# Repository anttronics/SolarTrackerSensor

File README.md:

## SolarTrackerSensor
A simple sensor circuit that uses photo-transistors and boolean logic to indicate if a solar panel is pointing straight at the sun. 

### Outputs 
- It produces 4 digital outputs to indicate if movement is required in up, down, left or right directions. Those outputs can be passed directly to a motor controller which can correct the mis-alignment. 
- It also produces horizontal, vertical and combined "busy" signals to allow independent, as well as overall enabling/disabling of the motors.

**Warning**: All outputs are unprotected, digital signal outputs and should not be used to drive any motors directly.

### Limit Switches
It has normally-closed (NC) limit switch inputs for all 4 directions, but requires at least the "east" and "down" switches for auto-parking to function. The "west" and "up" limit switches can be omitted/bypassed if the motion mechanism has sufficient range and/or limits implemented elsewhere.

### Auto-parking
When the ambient light level falls below the adjustable threshold, it will auto-park the panel in the "east" and "down" position. Without the auto-park function, in the summer months, the panel would be left pointing west at sunset. The sun would then rise behind the panel and tracking would not resume until late morning, when the sun moves n front of the panel again.

### Sensitivity
A common reference level for all 4 comparators is produced using a potentiometer as a voltage divider. The simplest way to set the sensitivity is to adjust it on a dark cloudy day, to a level just above the parking level. This way it won't try to auto-park the panel every time a cloud moves across the sun. 

### Assembly
The board is designed in 3 parts: 
- the "logic" part which contains all the main components,
- the "sensor" part which contains the photo-transistors and
- the "shield" parts. 

The "sensor" board has the same footprints on both sides, allowing assembly on the "N" or "S" side, depending on whether the sun will be tracked from the north or south hemisphere.

It can be separated from the "logic" board and connected with wires, or it can be kept attached to the "logic" board. The traces between the boards complete all the required connections between the two boards.

The "shield" parts, when soldered onto the "sensor" board, form a pyramid-shaped sun screen that cast a shadow on the photo-transistors when the panel is not correctly aligned.

### Power supply
Even though all the components on the board could handle a higher voltage, a stable 5V DC power supply is highly recommended to ensure the reference levels for the comparator are actually effective. 

### Future ideas
- Motor control board with sleep/periodic wake-up function for low power consumption
- Battery charging board with constant panel voltage or MPP tracking.

### How did we get here?
The prototype "ancestor" of this board has been keeping an A4-size 4V panel pointed at the sun through my office window for a few years already. It charges a 2S LiPo battery during the day which in turn is used as a power bank to charge my phone. 

The mechanical construction is showing its age and needs an overhaul. The plan is to switch from continuous rotation servos to DC gear motors for smoother movement and in the process, try to tidy up the electronics as well.

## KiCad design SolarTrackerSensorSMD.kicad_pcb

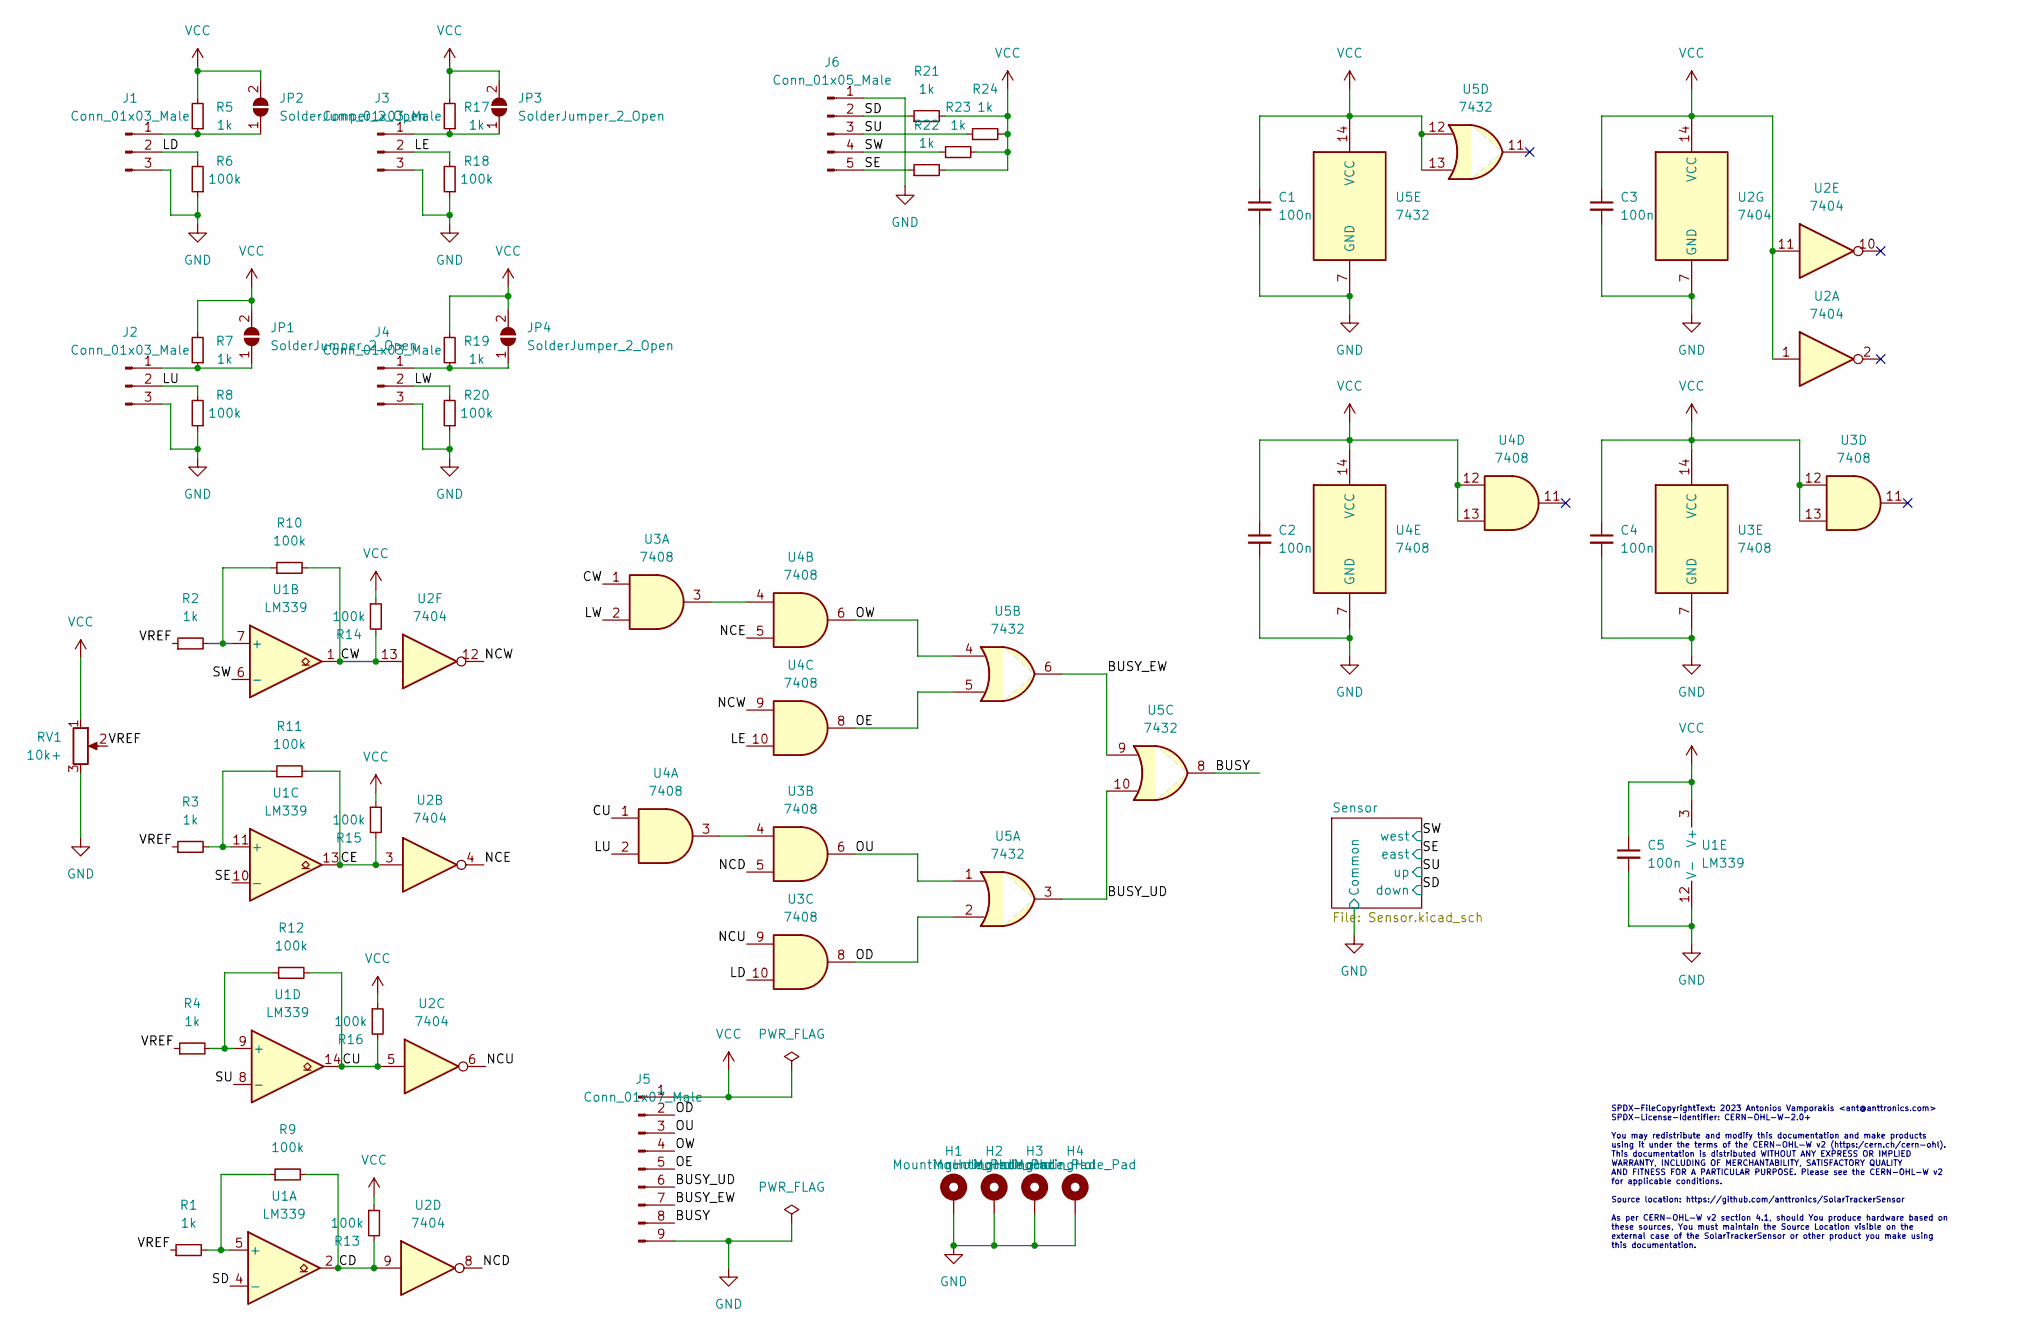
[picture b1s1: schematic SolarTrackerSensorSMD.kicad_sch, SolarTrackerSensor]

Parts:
C1, C2, C3, C4, C5: 100n; C_0603_1608Metric; MPN C282519
H1, H2, H3, H4: MountingHole_Pad; MountingHole_3.2mm_M3_DIN965_Pad
J1, J2, J3, J4: Conn_01x03_Male; PinHeader_1x03_P2.54mm_Vertical
J5: Conn_01x07_Male; PinHeader_1x09_P2.54mm_Vertical
J6: Conn_01x05_Male; PinHeader_1x05_P2.54mm_Vertical
JP1, JP2, JP3, JP4: SolderJumper_2_Open; SolderJumper-2_P1.3mm_Open_RoundedPad1.0x1.5mm
R1, R2, R3, R4, R5, R7, R17, R19, R21, R22, R23, R24: 1k; R_0603_1608Metric; MPN C3152127
R6, R8, R9, R10, R11, R12, R13, R14, R15, R16, R18, R20: 100k; R_0603_1608Metric; MPN C2907088
RV1: 10k+; Potentiometer_Bourns_3296W_Vertical; MPN C118963
U1: LM339; SOIC-14_3.9x8.7mm_P1.27mm; MPN C5456631
U2: 7404; SOIC-14_3.9x8.7mm_P1.27mm; MPN C141316
U3, U4: 7408; SOIC-14_3.9x8.7mm_P1.27mm; MPN C337768
U5: 7432; SOIC-14_3.9x8.7mm_P1.27mm; MPN C132988

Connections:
/BUSY: J5.8, U5.8
/BUSY_EW: J5.7, U5.6, U5.9
/BUSY_UD: J5.6, U5.3, U5.10
/CD: R9.2, R13.2, U1.2, U2.9
/CE: R11.2, R15.2, U1.13, U2.3
/CU: R12.2, R16.2, U1.14, U2.5, U4.1
/CW: R10.2, R14.2, U1.1, U2.13, U3.1
/LD: J1.2, R6.2, U3.10
/LE: J3.2, R18.2, U4.10
/LU: J2.2, R8.2, U4.2
/LW: J4.2, R20.2, U3.2
/NCD: U2.8, U3.5
/NCE: U2.4, U4.5
/NCU: U2.6, U3.9
/NCW: U2.12, U4.9
/OD: J5.2, U3.8, U5.2
/OE: J5.5, U4.8, U5.5
/OU: J5.3, U3.6, U5.1
/OW: J5.4, U4.6, U5.4
/SD: J6.2, R21.1, U1.4 (-); also elsewhere on the board
/SE: J6.5, R22.1, U1.10 (-); also elsewhere on the board
/SU: J6.3, R24.1, U1.8 (-); also elsewhere on the board
/SW: J6.4, R23.1, U1.6 (-); also elsewhere on the board
/VREF: R1.1, R2.1, R3.1, R4.1, RV1.2
GND: C1.2, C2.2, C3.2, C4.2, C5.2, H1.1, H2.1, H3.1, H4.1, J1.3, J2.3, J3.3, J4.3, J5.9, J6.1, R6.1, R8.1, R18.1, R20.1, RV1.3, U1.12 (V-), U2.7 (GND), U3.7 (GND), U4.7 (GND), U5.7 (GND); also elsewhere on the board
unnamed: J1.1, JP2.1 (A), R5.1
unnamed: J2.1, JP1.1 (A), R7.1
unnamed: J3.1, JP3.1 (A), R17.1
unnamed: J4.1, JP4.1 (A), R19.1
unnamed: R1.2, R9.1, U1.5 (+)
unnamed: R2.2, R10.1, U1.7 (+)
unnamed: R3.2, R11.1, U1.11 (+)
unnamed: R4.2, R12.1, U1.9 (+)
unnamed: U3.3, U4.4
unnamed: U3.4, U4.3
VCC: C1.1, C2.1, C3.1, C4.1, C5.1, J5.1, JP1.2 (B), JP2.2 (B), JP3.2 (B), JP4.2 (B), R5.2, R7.2, R13.1, R14.1, R15.1, R16.1, R17.2, R19.2, R21.2, R22.2, R23.2, R24.2, RV1.1, U1.3 (V+), U2.1, U2.11, U2.14 (VCC), U3.12, U3.13, U3.14 (VCC), U4.12, U4.13, U4.14 (VCC), U5.12, U5.13, U5.14 (VCC)

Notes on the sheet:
SPDX-FileCopyrightText: 2023 Antonios Vamporakis <ant@anttronics.com> SPDX-License-Identifier: CERN-OHL-W-2.0+ You may redistribute and modify this documentation and make products using it under the terms of the CERN-OHL-W v2 (https:/cern.ch/cern-ohl). This documentation is distributed WITHOUT ANY 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

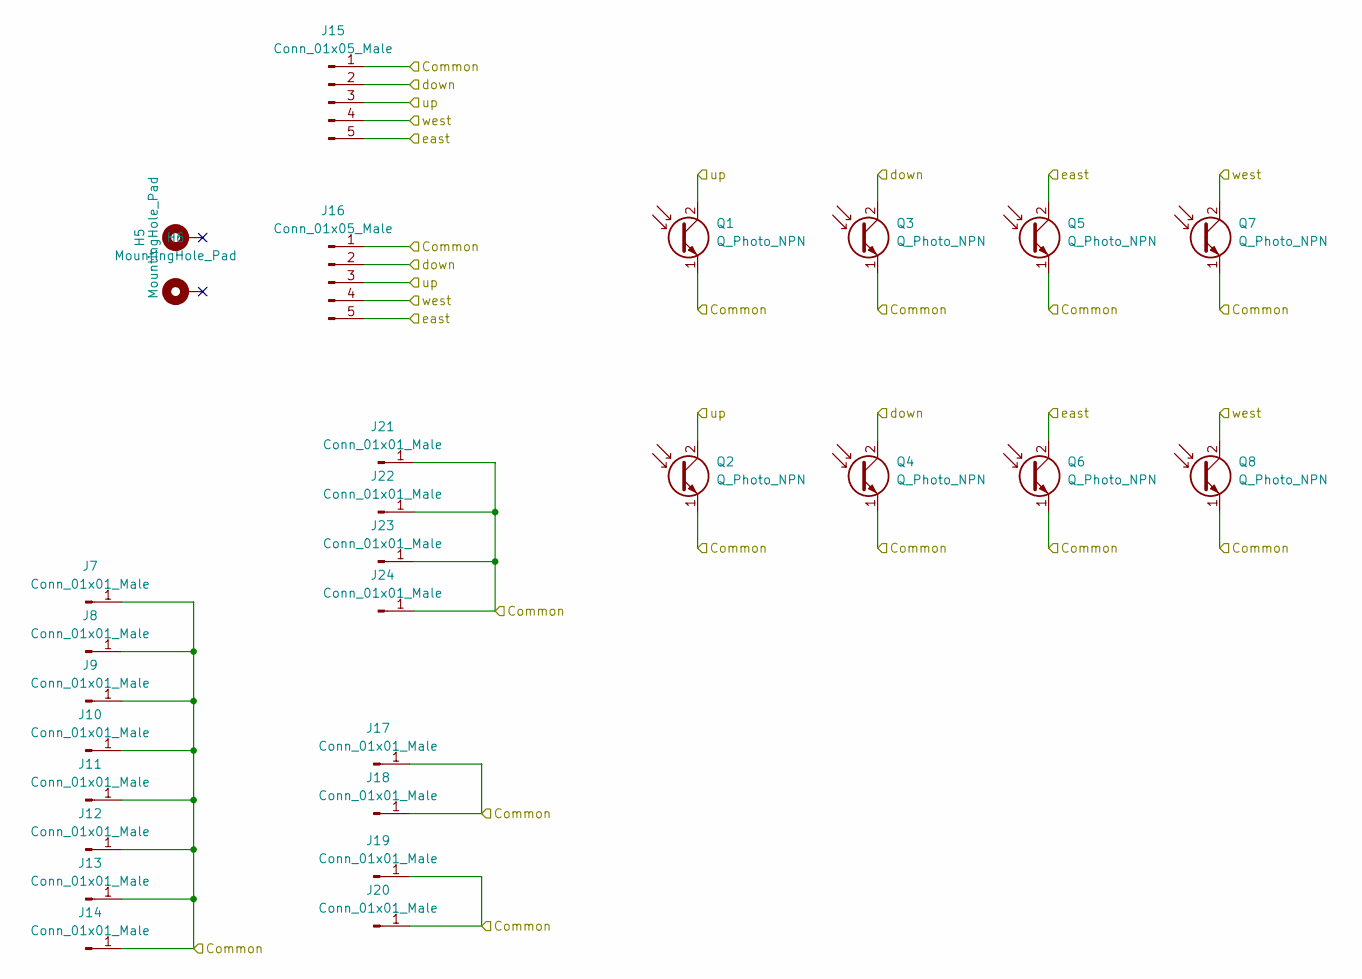
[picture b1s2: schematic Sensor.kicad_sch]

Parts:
H5, H6: MountingHole_Pad; MountingHole_3.2mm_M3_DIN965_Pad
J7, J8, J9, J10, J11, J12, J13, J14: Conn_01x01_Male; TestPoint_Pad_4.0x4.0mm
J15, J16: Conn_01x05_Male; PinHeader_1x05_P2.54mm_Vertical
J17, J18, J19, J20: Conn_01x01_Male; TestPoint_Pad_D4.0mm
J21, J22, J23, J24: Conn_01x01_Male; TestPoint_THTPad_D4.0mm_Drill2.0mm
Q1, Q2, Q3, Q4, Q5, Q6, Q7, Q8: Q_Photo_NPN; LED_0603_1608Metric; MPN C146233

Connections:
/SD: J15.2, J16.2, Q3.2 (C), Q4.2 (C); also elsewhere on the board
/SE: J15.5, J16.5, Q5.2 (C), Q6.2 (C); also elsewhere on the board
/SU: J15.3, J16.3, Q1.2 (C), Q2.2 (C); also elsewhere on the board
/SW: J15.4, J16.4, Q7.2 (C), Q8.2 (C); also elsewhere on the board
GND: J7.1, J8.1, J9.1, J10.1, J11.1, J12.1, J13.1, J14.1, J15.1, J16.1, J17.1, J18.1, J19.1, J20.1, J21.1, J22.1, J23.1, J24.1, Q1.1 (E), Q2.1 (E), Q3.1 (E), Q4.1 (E), Q5.1 (E), Q6.1 (E), Q7.1 (E), Q8.1 (E); also elsewhere on the board

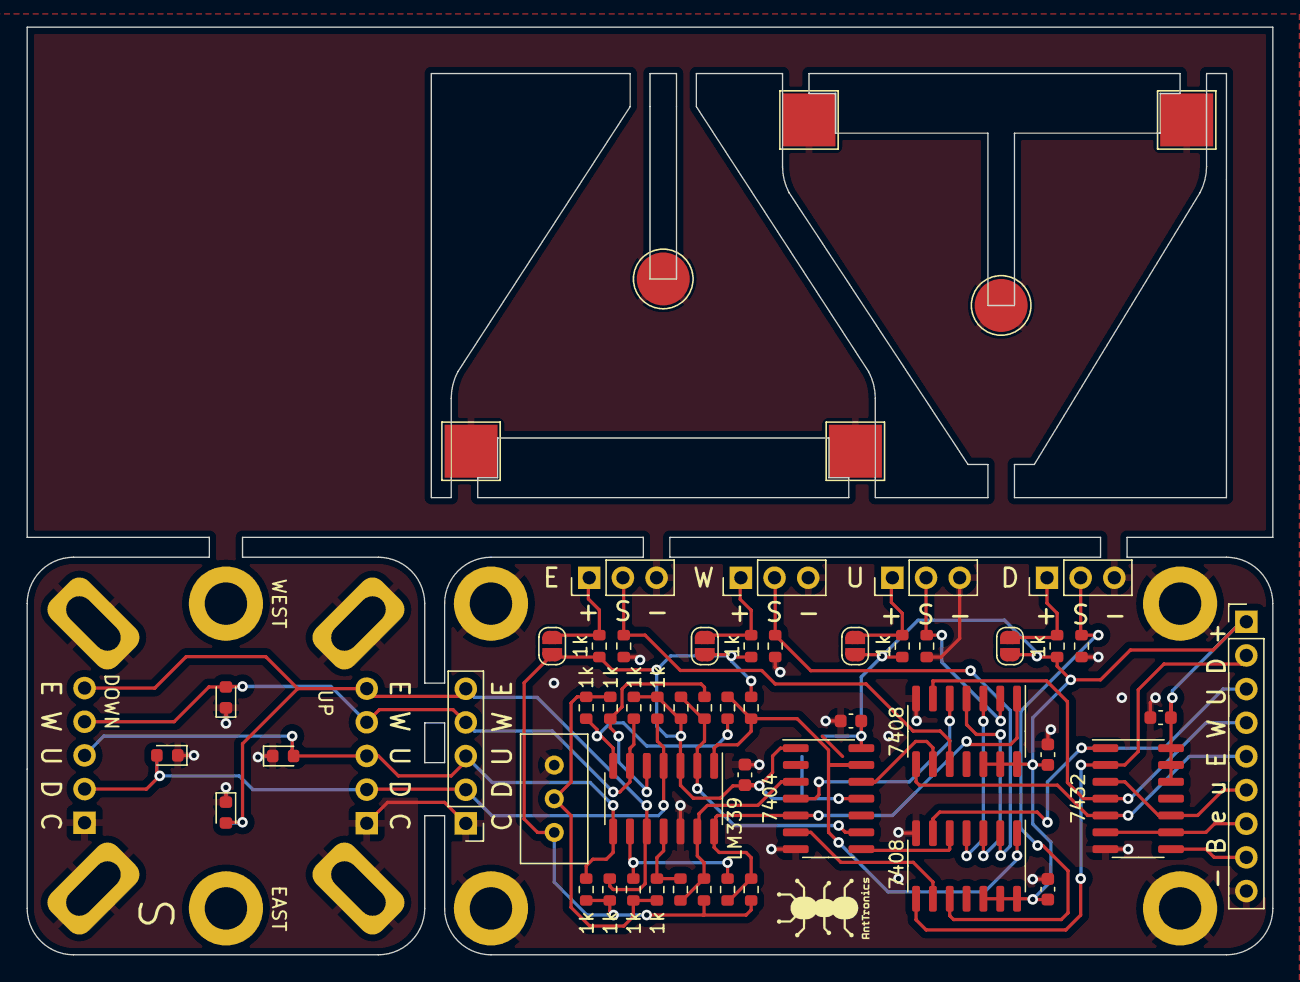
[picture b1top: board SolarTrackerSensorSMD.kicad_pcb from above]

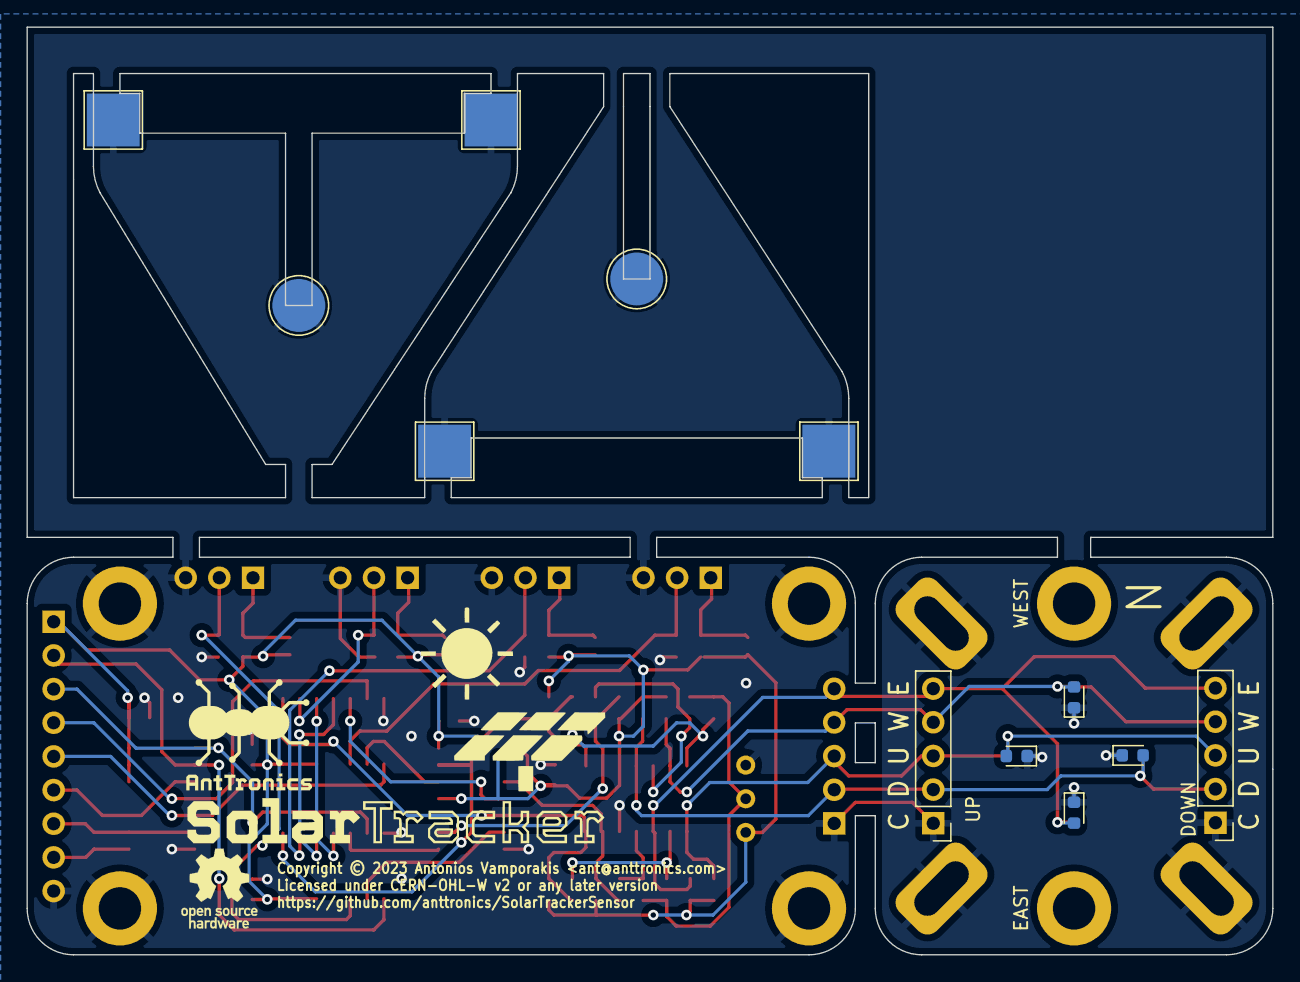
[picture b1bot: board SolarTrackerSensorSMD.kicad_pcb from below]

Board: 2 copper layers, 94.0 x 69.9 mm, 77 parts (12 on the bottom side), 36 nets.

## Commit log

2023-07-08 Replace Idle with Busy_UD & Busy_EW
2023-12-11 Remove ignored files
2023-12-11 Remove loose schematic
2023-12-11 add readme
2023-12-14 restore Sensor.kicad_sch
2023-12-16 Add licence & reshuffle silkscreen graphics
2023-12-20 CERN OHL W seems more appropriate

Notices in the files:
SolarTrackerSensorSMD.kicad_pcb:
Copyright © 2023 Antonios Vamporakis
Licensed under CERN-OHL-W v2 or any later version
As per CERN-OHL-W v2 section 4.1, should You produce hardware based on
